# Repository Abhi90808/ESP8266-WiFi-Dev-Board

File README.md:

# ESP8266 WiFi Development Board

A custom ESP8266-based WiFi development board designed in KiCad 8, featuring onboard USB-to-serial, 3.3V regulation, and a breadboard-friendly pinout — perfect for IoT prototyping.

---

## Features
- ESP8266 (ESP-12E/F module) WiFi MCU
- Onboard USB-to-Serial (CH340G)
- 3.3V LDO regulator (AMS1117-3.3)
- Auto-reset circuit for one-click flashing
- All GPIO pins broken out to 2.54mm headers
- Flash and Reset buttons onboard
- Power LED and user LED (GPIO2)

## Specifications

| Parameter | Value |
|-----------|-------|
| Module | ESP-12E / ESP-12F |
| MCU | Tensilica L106 (32-bit) |
| Clock Speed | 80MHz / 160MHz |
| WiFi | 802.11 b/g/n (2.4GHz) |
| Operating Voltage | 3.3V |
| USB Input | 5V via Micro USB |
| Flash Memory | 4MB |
| GPIO Pins | 11 usable |
| PCB Layers | 2 |
| Designed With | KiCad 8 |

## Project Structure

```
├── Schematic/       # KiCad schematic (.kicad_sch, PDF)
├── PCB/             # PCB layout (.kicad_pcb, .kicad_pro)
├── Gerbers/         # Fabrication files
├── BOM/             # Bill of materials (CSV)
├── 3D/              # 3D model (.step)
└── Images/          # PCB renders and schematic screenshots
```

## How It Works

The CH340G converts USB to UART for programming. The auto-reset circuit uses transistors on the DTR/RTS lines to automatically pull GPIO0 LOW and reset the ESP8266 before flashing — no manual button pressing needed.

## Programming

1. Install the ESP8266 board in Arduino IDE via Boards Manager
2. Select **Generic ESP8266 Module** or **NodeMCU 1.0**
3. Connect via Micro USB and select the correct COM port
4. Upload directly — auto-reset handles the rest

## Bill of Materials (Summary)

| Component | Value | Qty |
|-----------|-------|-----|
| WiFi Module | ESP-12F | 1 |
| USB-Serial IC | CH340G | 1 |
| LDO Regulator | AMS1117-3.3V | 1 |
| Capacitors | 100nF, 10µF | 4 |
| Transistors | BC817 | 2 |
| Buttons | Tactile | 2 |
| USB Connector | Micro-B | 1 |

## Fabrication

Gerber files are in `/Gerbers`, ready for JLCPCB, PCBWay, or similar.

## License

This project is licensed under the [CERN Open Hardware Licence Version 2 - Strongly Reciprocal (CERN OHL-S v2)](https://ohwr.org/cern_ohl_s_v2.txt).

## Author

**Abhi90808** — [GitHub Profile](https://github.com/Abhi90808)

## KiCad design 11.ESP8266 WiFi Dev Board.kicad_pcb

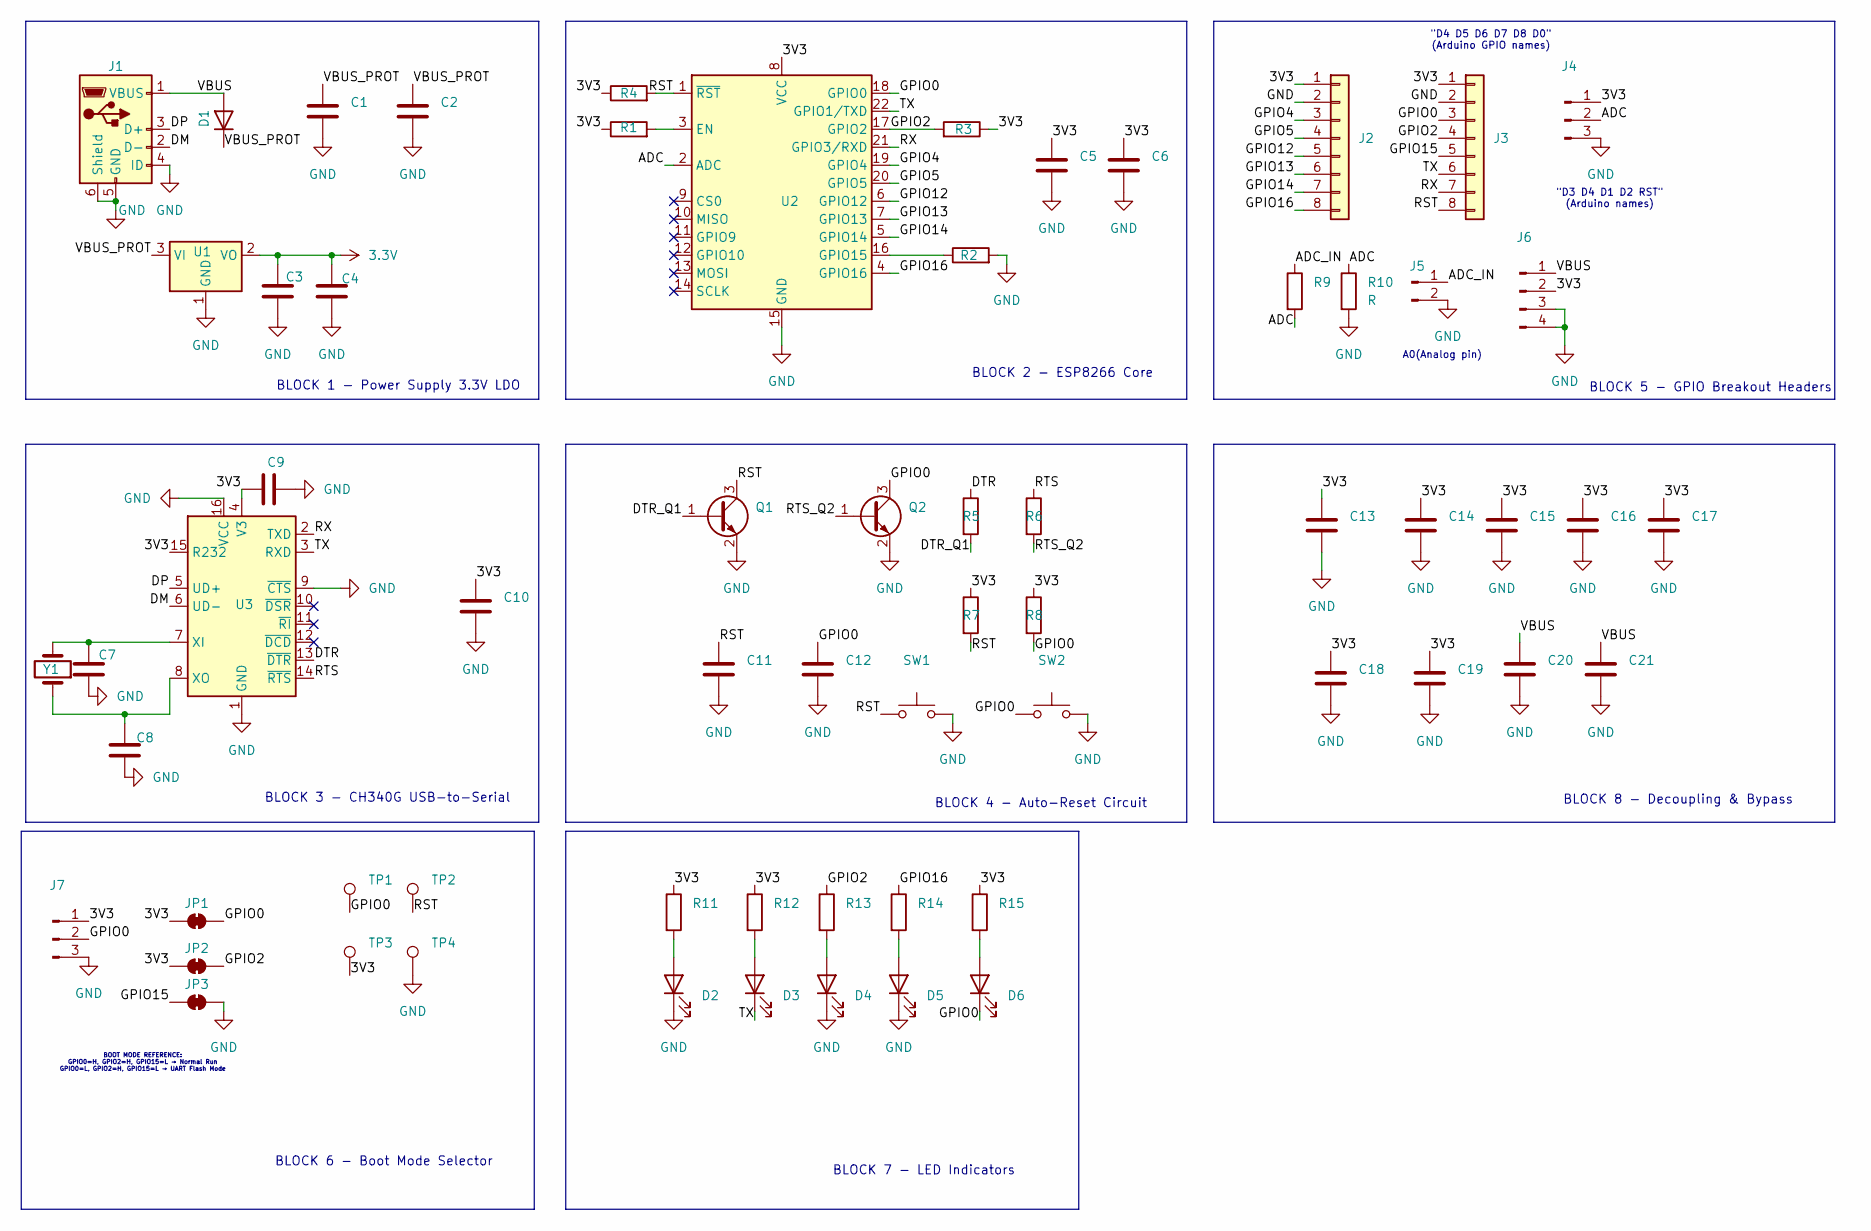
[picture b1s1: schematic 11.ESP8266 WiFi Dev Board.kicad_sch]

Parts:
C1, C3, C5: 10uf; C_0805_2012Metric
C2, C4, C10, C11, C12, C15, C16, C17: 100nf; C_0402_1005Metric
C6, C21: 100uF; C_0402_1005Metric
C7, C8: 22PF; C_0402_1005Metric
C9: 100nF; C_0402_1005Metric
C13, C20: 100uF; C_1210_3225Metric
C14: 47uF; C_1210_3225Metric
C18, C19: 10nf; C_0402_1005Metric
D1: D1N5819; D_SOD-123
D2, D3, D4, D5, D6: PWR_LED; LED_0805_2012Metric
J1: USB_B_Micro; USB_Micro-B_Amphenol_10103594-0001LF_Horizontal
J2: GPIO_LEFT; PinHeader_1x08_P2.54mm_Vertical
J3: GPIO_RIGHT; PinHeader_1x08_P2.54mm_Vertical
J4: ANALOG; PinHeader_1x03_P2.54mm_Vertical
J5: ADC_INPUT; PinHeader_1x02_P2.54mm_Vertical
J6: POWER_HEADER; PinHeader_1x04_P2.54mm_Vertical
J7: BOOT_SEL; PinHeader_1x03_P2.54mm_Vertical
JP1: RUN_MODE; PinHeader_1x02_P2.54mm_Vertical
JP2: GPIO2_PULL; SolderJumper-2_P1.3mm_Open_RoundedPad1.0x1.5mm
JP3: GPIO15_PULL; SolderJumper-2_P1.3mm_Open_RoundedPad1.0x1.5mm
Q1, Q2: BC817; SOT-23
R1, R2, R3, R4, R5, R6, R7, R8: 10k; R_0402_1005Metric
R9: 220k; R_0402_1005Metric
R10: R; R_0402_1005Metric
R11, R12: 1k; R_0402_1005Metric
R13: 470R; R_0402_1005Metric
R14: 470ohm; R_0402_1005Metric
R15: 1K; R_0402_1005Metric
SW1: RESET; SW_PUSH_6mm_H5mm
SW2: FLASH; SW_PUSH_6mm_H5mm
TP1, TP2, TP3, TP4: TestPoint; TestPoint_Pad_D1.5mm
U1: AMS1117-3.3; SOT-223-3_TabPin2
U2: ESP-12E
U3: CH340G; SOIC-16_3.9x9.9mm_P1.27mm
Y1: 12MHZ; Crystal_SMD_3225-4Pin_3.2x2.5mm

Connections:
3.3V: C3.1, C4.1, U1.2 (VO)
/3V3: C5.1, C6.1, C9.1, C10.1, C13.1, C14.1, C15.1, C16.1, C17.1, C18.1, C19.1, J2.1, J3.1, J4.1, J6.2, J7.1, JP1.1 (A), JP2.1 (A), R1.1, R3.1, R4.1, R7.1, R8.1, R11.1, R12.1, R15.1, TP3.1, U2.8 (VCC), U3.4 (V3), U3.15 (R232)
/ADC: J4.2, R9.2, R10.1, U2.2 (ADC)
/ADC_IN: J5.1, R9.1
/DM: J1.2 (D-), U3.6 (UD-)
/DP: J1.3 (D+), U3.5 (UD+)
/DTR: R5.1, U3.13 (~DTR)
/DTR_Q1: Q1.1 (B), R5.2
/GPIO0: C12.1, D6.1 (K), J3.3, J7.2, JP1.2 (B), Q2.3 (C), R8.2, SW2.1, TP1.1, U2.18 (GPIO0)
/GPIO2: J3.4, JP2.2 (B), R3.2, R13.1, U2.17 (GPIO2)
/GPIO4: J2.3, U2.19 (GPIO4)
/GPIO5: J2.4, U2.20 (GPIO5)
/GPIO12: J2.5, U2.6 (GPIO12)
/GPIO13: J2.6, U2.7 (GPIO13)
/GPIO14: J2.7, U2.5 (GPIO14)
/GPIO15: J3.5, JP3.1 (A)
/GPIO16: J2.8, R14.1, U2.4 (GPIO16)
/RST: C11.1, J3.8, Q1.3 (C), R4.2, R7.2, SW1.1, TP2.1, U2.1 (~RST)
/RTS: R6.1, U3.14 (~RTS)
/RTS_Q2: Q2.1 (B), R6.2
/RX: J3.7, U2.21 (GPIO3/RXD), U3.2 (TXD)
/TX: D3.1 (K), J3.6, U2.22 (GPIO1/TXD), U3.3 (RXD)
/VBUS: C20.1, C21.1, D1.2 (A), J1.1 (VBUS), J6.1
/VBUS_PROT: C1.1, C2.1, D1.1 (K), U1.3 (VI)
GND: C1.2, C2.2, C3.2, C4.2, C5.2, C6.2, C7.2, C8.2, C9.2, C10.2, C11.2, C12.2, C13.2, C14.2, C15.2, C16.2, C17.2, C18.2, C19.2, C20.2, C21.2, D2.1 (K), D4.1 (K), D5.1 (K), J1.4 (ID), J1.5 (GND), J1.6 (Shield), J2.2, J3.2, J4.3, J5.2, J6.3, J6.4, J7.3, JP3.2 (B), Q1.2 (E), Q2.2 (E), R2.2, R10.2, SW1.2, SW2.2, TP4.1, U1.1 (GND), U2.15 (GND), U3.1 (GND), U3.9 (~CTS), U3.16 (VCC)
unnamed: D2.2 (A), R11.2
unnamed: D3.2 (A), R12.2
unnamed: D4.2 (A), R13.2
unnamed: D5.2 (A), R14.2
unnamed: D6.2 (A), R15.2
unnamed: R1.2, U2.3 (EN)
unnamed: R2.1, U2.16 (GPIO15)
unnamed: C7.1, U3.7 (XI), Y1.2
unnamed: C8.1, U3.8 (XO), Y1.1

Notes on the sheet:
BLOCK 1 - Power Supply 3.3V LDO
BLOCK 4 - Auto-Reset Circuit
BLOCK 2 - ESP8266 Core
"D4 D5 D6 D7 D8 D0" (Arduino GPIO names)
BLOCK 3 - CH340G USB-to-Serial
A0(Analog pin)
BOOT MODE REFERENCE: GPIO0=H, GPIO2=H, GPIO15=L → Normal Run GPIO0=L, GPIO2=H, GPIO15=L → UART Flash Mode
BLOCK 5 - GPIO Breakout Headers
BLOCK 8 - Decoupling & Bypass
"D3 D4 D1 D2 RST" (Arduino names)
BLOCK 7 - LED Indicators
BLOCK 6 - Boot Mode Selector

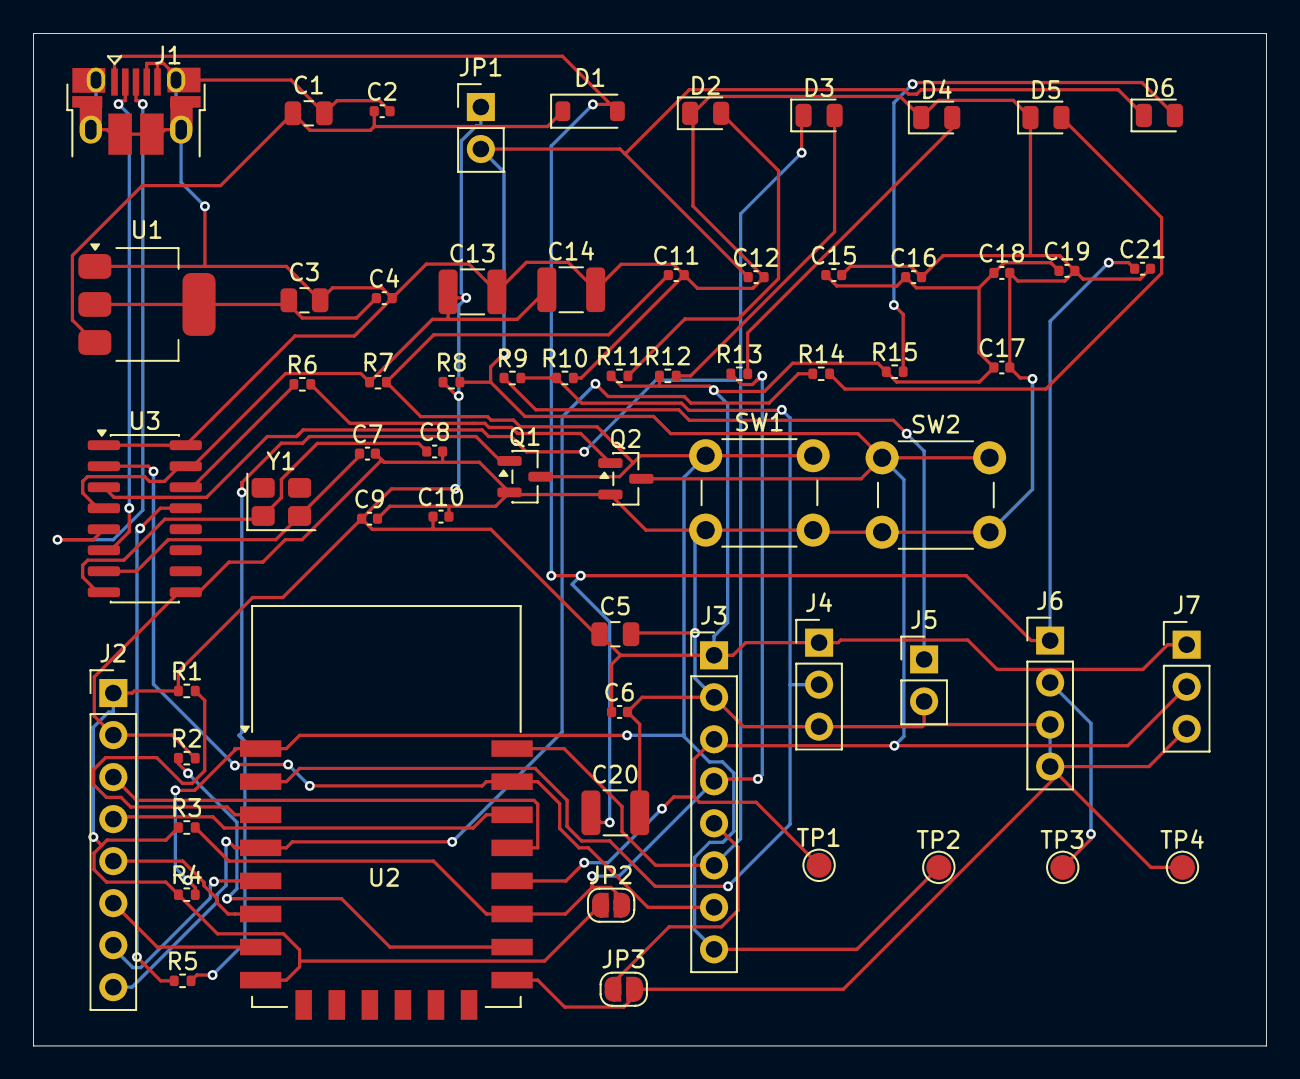
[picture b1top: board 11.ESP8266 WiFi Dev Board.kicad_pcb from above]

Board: 2 copper layers, 74.5 x 61.2 mm, 64 parts (0 on the bottom side), 34 nets.
